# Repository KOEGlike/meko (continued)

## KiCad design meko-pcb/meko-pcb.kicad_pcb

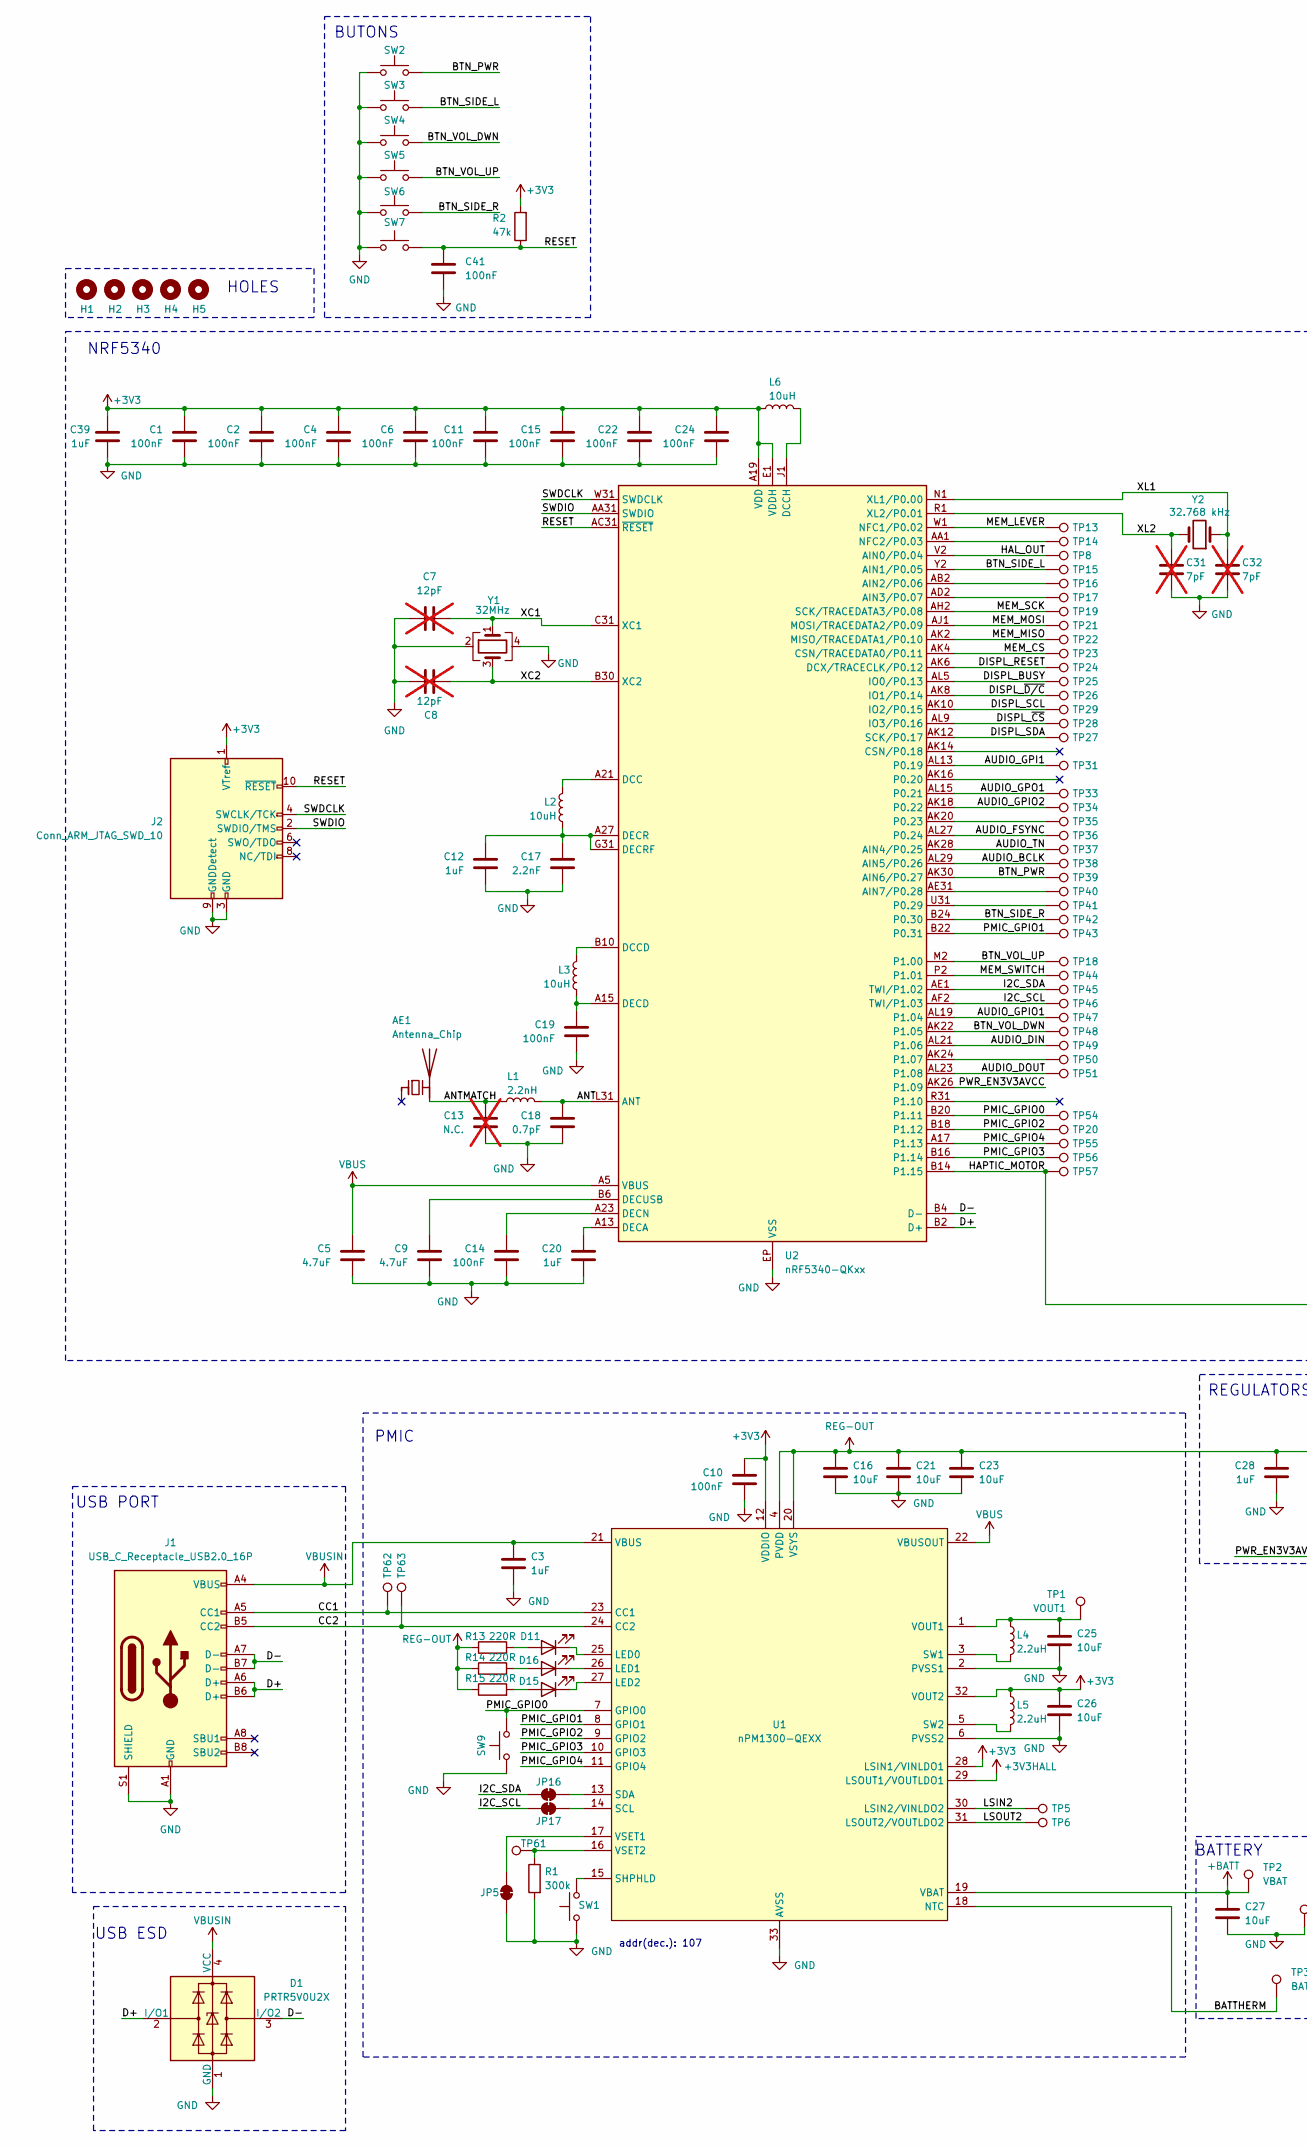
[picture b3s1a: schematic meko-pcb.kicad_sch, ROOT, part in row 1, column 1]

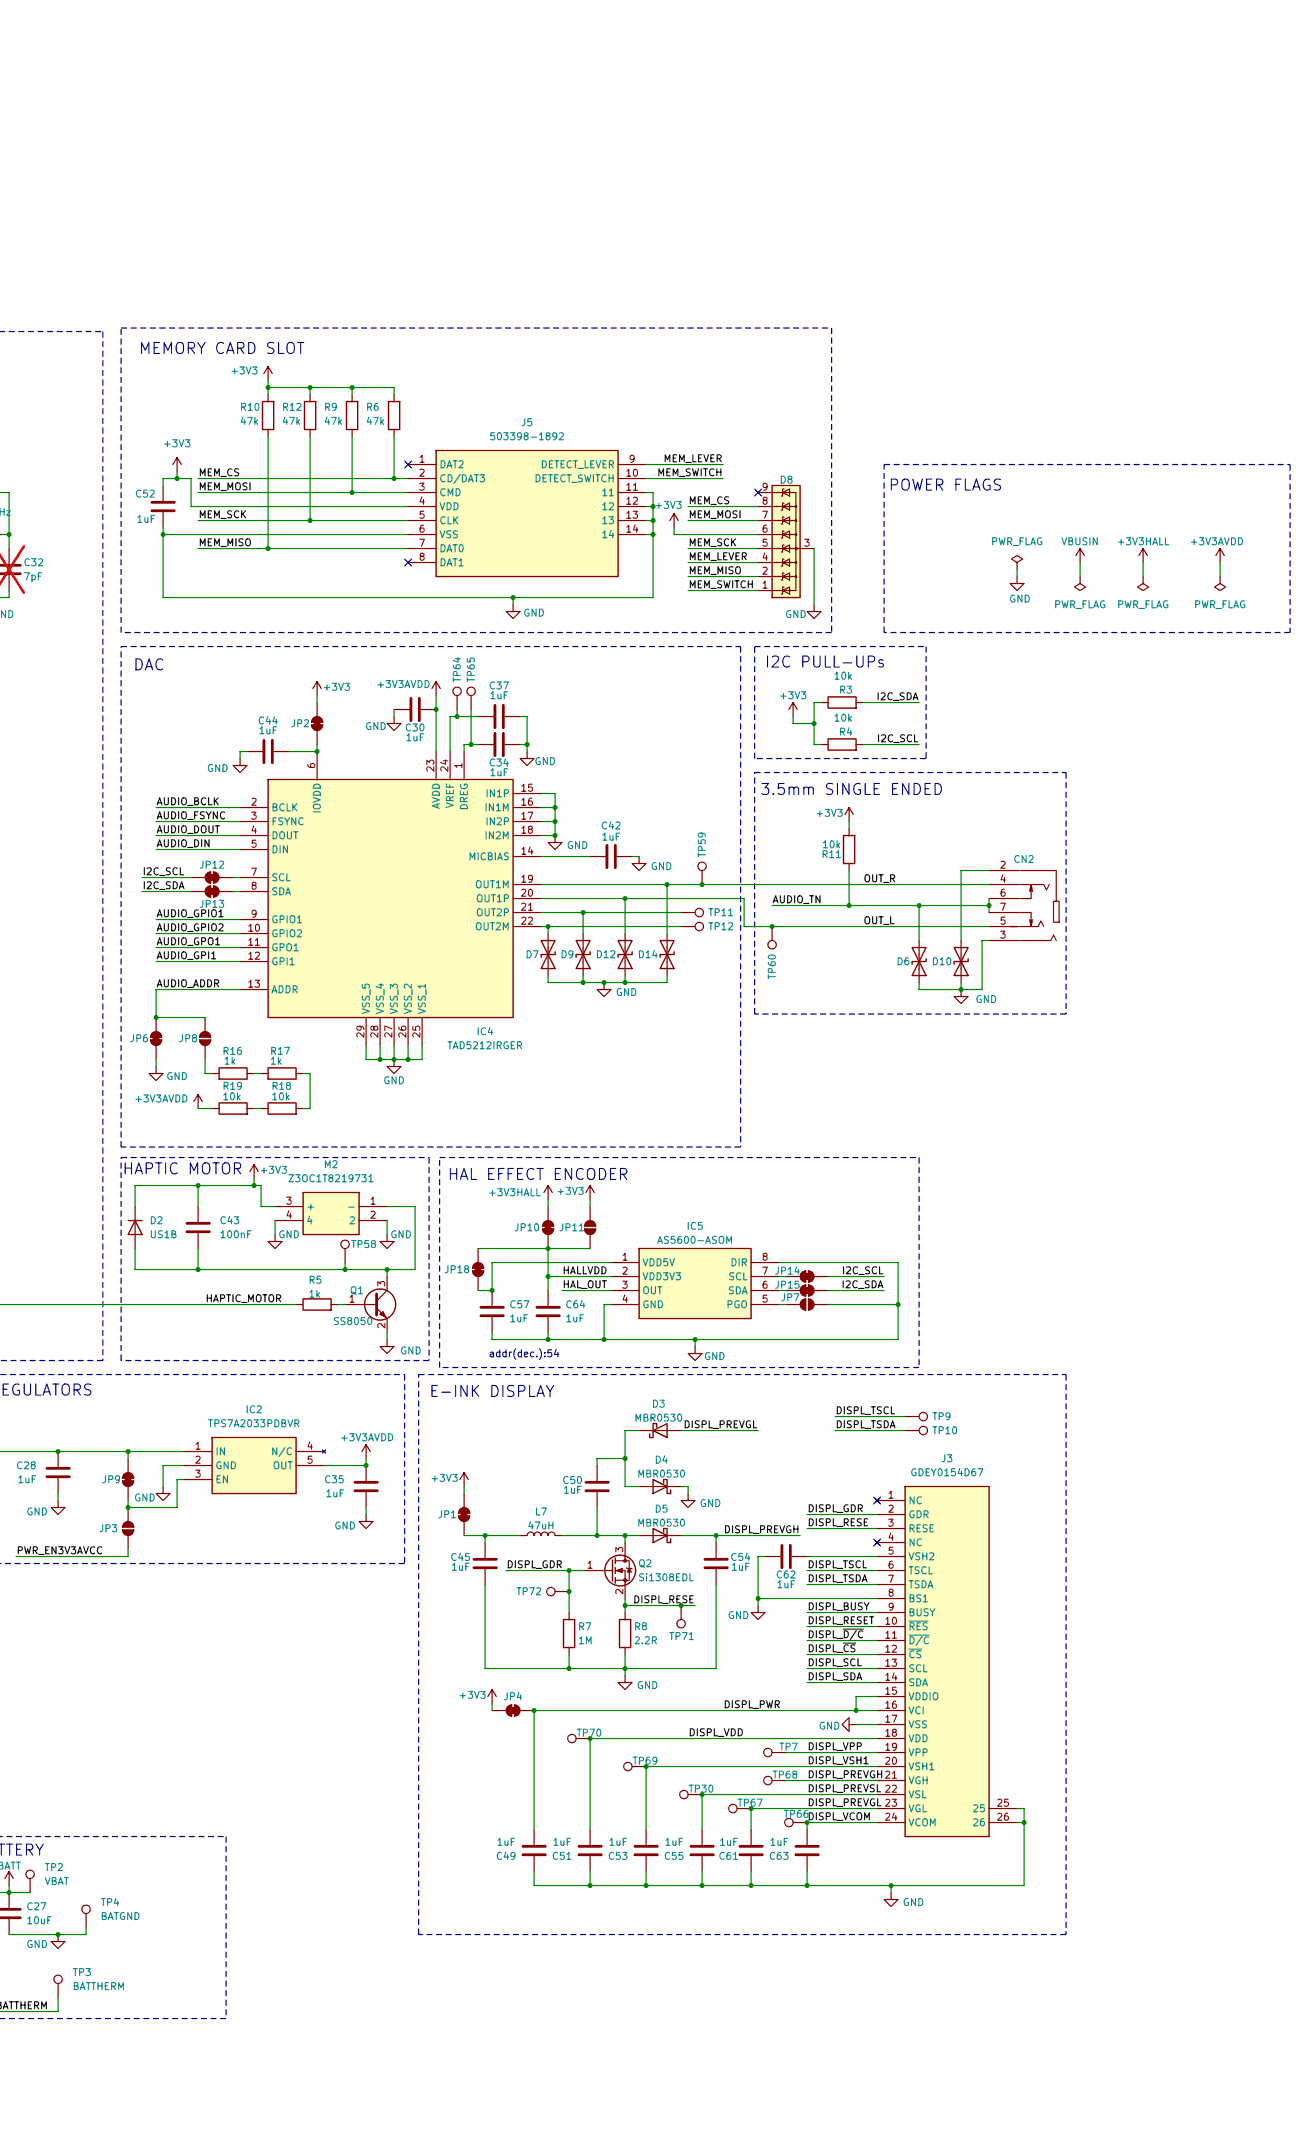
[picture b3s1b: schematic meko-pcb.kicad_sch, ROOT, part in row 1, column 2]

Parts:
AE1: Antenna_Chip; D_1206_3216Metric; MPN ANT3216LL00R2400A; LCSC C293767
C1, C2, C4, C6, C10, C11, C14, C15, C19, C22, C24, C41, C43: 100nF; C_0603_1608Metric; MPN CC0603KRX7R9BB104; LCSC C14663
C3, C12, C20, C28, C30, C34, C35, C37, C39, C42, C44, C45, C49, C50, C51, C52, C53, C54, C55, C57, C61, C62, C63, C64: 1uF; C_0603_1608Metric; MPN CL10A105KB8NNNC; LCSC C15849
C5, C9: 4.7uF; C_0603_1608Metric; MPN CL10A475KP8NNNC; LCSC C19666
C7, C8: 12pF; C_0603_1608Metric; MPN CL10C120JB8NNNC; LCSC C38523; not fitted
C13: N.C.; C_0603_1608Metric; not fitted
C16, C21, C23, C25, C26, C27: 10uF; C_0603_1608Metric; MPN CL10A106KP8NNNC; LCSC C19702
C17: 2.2nF; C_0603_1608Metric; MPN FCC0603B222K500CT; LCSC C5137562
C18: 0.7pF; C_0603_1608Metric; MPN CC0603BRNPO9BNR70; LCSC C501844
C31, C32: 7pF; C_0603_1608Metric; not fitted
CN2: AUDIO-SMD_PJ-342; MPN PJ-342; LCSC Part Name 3.5mm耳机座
D1: PRTR5V0U2X; SOT-143; MPN PRTR5V0U2X,215; LCSC C12333
D2: US1B; D_SMA; MPN US1B; LCSC C18199126
D3, D4, D5: MBR0530; D_SOD-123; MPN MBR0530T1G; LCSC C82046
D6, D7, D9, D10, D12, D14: D_TVS; D_SOD-323F; MPN PESD5V0V1BA; LCSC C29779756
D8: D3V3X8U9LP3810; Diodes_UDFN3810-9_TYPE_B-better-pinout; MPN D3V3F8U9LP3810-7; LCSC C3715130
D11: Orange; LED_0603_1608Metric; MPN XL-1608UOC-06; LCSC C965800
D15: white; LED_0603_1608Metric; MPN XL-1608UWC-04; LCSC C965808
D16: blue; LED_0603_1608Metric; MPN F.0603.00048/P2-0603W6YS2-06T-002; LCSC C7496823
H1, H2, H3, H4, H5: MountingHole; MountingHole_1.8mm_M1.6
IC2: TPS7A2033PDBVR; SOT95P280X145-5N; MPN TPS7A2033PDBVR; Mouser Part Number 595-TPS7A2033PDBVR
IC4: TAD5212IRGER; TAD5112IRGER; MPN TAD5212IRGER; LCSC C45068920
IC5: AS5600-ASOM; SOIC127P600X175-8N; MPN AS5600-ASOT; LCSC C499458
J1: USB_C_Receptacle_USB2.0_16P; USB_C_Receptacle_G-Switch_GT-USB-7010ASV; MPN GT-USB-7010ASV; LCSC C2988369
J2: Conn_ARM_JTAG_SWD_10; PinHeader_2x05_P1.27mm_Vertical
J3: GDEY0154D67; FPC-SMD_24P-P0.50_FPC-05FB-24PH20; MPN FPC-05FB-24PH20; Mouser Part Number 798-FH34SRJ24S05SH99
J5: 503398-1892; 5033981892; MPN 503398-1892; Mouser Part Number 538-503398-1892
JP1, JP2, JP4, JP5, JP6, JP9, JP10, JP12, JP13, JP14, JP15, JP16, JP17, JP18: SolderJumper_2_Bridged; SolderJumper-2_P1.3mm_Bridged_RoundedPad1.0x1.5mm
JP3, JP7, JP8, JP11: SolderJumper_2_Open; SolderJumper-2_P1.3mm_Open_RoundedPad1.0x1.5mm
L1: 2.2nH; L_0603_1608Metric; MPN LQG18HN2N2S00D; LCSC C113061
L2, L3, L6: 10uH; L_0805_2012Metric; MPN SLM2012100MIT; LCSC C2831365
L4, L5: 2.2uH; L_0805_2012Metric; MPN DFE201210U-2R2M=P2; LCSC C2049745
L7: 47uH; L_0805_2012Metric; MPN MLZ2012M470WT000; LCSC C383408
M2: Z3OC1T8219731; Manufacturer_Part_Number Z3OC1T8219731; LCSC C2894731
Q1: SS8050; SOT-23; MPN SS8050-HF; LCSC C5179688
Q2: Si1308EDL; SOT-323_SC-70; MPN SI1308EDL-T1-GE3; LCSC C469327
R1: 300k; R_0603_1608Metric; MPN FRC0603F3003TS; LCSC C23024
R2, R6, R9, R10, R12: 47k; R_0603_1608Metric; MPN FRC0603F4702TS; LCSC C25819
R3, R4, R11, R18, R19: 10k; R_0603_1608Metric; MPN 0603WAF1002T5E; LCSC C25804
R5, R16, R17: 1k; R_0603_1608Metric; MPN RC0603FR-071KL; LCSC C21190
R7: 1M; R_0603_1608Metric; MPN RC0603FR-071ML; LCSC C22935
R8: 2.2R; R_0603_1608Metric; MPN FRC0603J2R2TS; LCSC C2930032
R13, R14, R15: 220R; R_0603_1608Metric; MPN RC0603FR-07220RL; LCSC C22962
SW1, SW7, SW9: SW_Push; SW_Push_SPST_NO_Alps_SKRK; MPN TS-1088-AR02016; LCSC C720477
SW2, SW3, SW4, SW5, SW6: SW_Push; SW_Push_1P1T-MP_NO_Horizontal_Alps_SKRTLAE010; MPN SKRTLAE010; LCSC C110293
TP1: VOUT1; TestPoint_Pad_D1.0mm
TP2: VBAT; TestPoint_Pad_D1.5mm
TP3: BATTHERM; TestPoint_Pad_D1.5mm
TP4: BATGND; TestPoint_Pad_D1.5mm
TP5, TP11, TP13, TP15, TP18, TP19, TP20, TP23, TP26, TP29, TP35, TP38, TP41, TP46, TP49, TP63, TP65: DISPL_SCL; TestPoint_Pad_D1.0mm
TP6, TP7, TP8, TP9, TP10, TP12, TP14, TP16, TP17, TP21, TP22, TP24, TP25, TP27, TP28, TP30, TP31, TP33, TP34, TP36, TP37, TP39, TP40, TP42, TP43, TP44, TP45, TP47, TP48, TP50, TP51, TP54, TP55, TP56, TP57, TP58, TP59, TP60, TP61, TP62, TP64, TP66, TP67, TP68, TP69, TP70, TP71, TP72: DISPL_SDA; TestPoint_Pad_D1.0mm
U1: nPM1300-QEXX; QFN-32-1EP_5x5mm_P0.5mm_EP3.6x3.6mm_ThermalVias; MPN nPM1300-QEAA-R7; LCSC C7501206
U2: nRF5340-QKxx; Nordic_AQFN-94-1EP_7x7mm_P0.4mm; MPN NRF5340-QKAA-R; LCSC C3015611
Y1: 32MHz; Crystal_SMD_2520-4Pin_2.5x2.0mm; MPN 2TJ432000NYFBC; LCSC C2149238
Y2: 32.768 kHz; Crystal_SMD_3215-2Pin_3.2x1.5mm; MPN XKXGI-SUA-32.768K; LCSC C90945

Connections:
+3V3: C1.1, C2.1, C4.1, C6.1, C10.1, C11.1, C15.1, C22.1, C24.1, C26.1, C39.1, C43.1, C52.1, D2.1 (K), D8.6 (Line-7), J2.1 (VTref), J5.4 (VDD), JP1.2 (B), JP2.2 (B), JP4.2 (B), JP11.1 (A), L5.1, L6.2, M2.3 (+), R2.2, R3.1, R4.1, R6.2, R9.2, R10.2, R11.2, R12.2, U1.12 (VDDIO), U1.28 (LSIN1/VINLDO1), U1.32 (VOUT2), U2.A19 (VDD), U2.AC1 (VDD), U2.AG1 (VDD), U2.AJ31 (VDD), U2.AL3 (VDD), U2.AL7 (VDD), U2.AL11 (VDD), U2.AL17 (VDD), U2.AL25 (VDD), U2.B8 (VDD), U2.B28 (VDD), U2.C1 (VDD), U2.E1 (VDDH), U2.E31 (VDD), U2.L1 (VDD), U2.N31 (VDD), U2.U1 (VDD)
+3V3AVDD: C30.1, C35.1, IC2.5 (OUT), IC4.23 (AVDD), R19.1
+3V3HALL: JP10.2 (B), U1.29 (LSOUT1/VOUTLDO1)
+BATT: C27.1, TP2.1, U1.19 (VBAT)
/ANT: C18.1, L1.1, U2.L31 (ANT)
/ANTMATCH: AE1.2 (PCB_Trace), C13.1, L1.2
/AUDIO_ADDR: IC4.13 (ADDR), JP6.2 (B), JP8.1 (A)
/AUDIO_BCLK: IC4.2 (BCLK), TP38.1, U2.AL29 (AIN5/P0.26)
/AUDIO_DIN: IC4.5 (DIN), TP49.1, U2.AL21 (P1.06)
/AUDIO_DOUT: IC4.4 (DOUT), TP51.1, U2.AL23 (P1.08)
/AUDIO_FSYNC: IC4.3 (FSYNC), TP36.1, U2.AL27 (P0.24)
/AUDIO_GPI1: IC4.12 (GPI1), TP31.1, U2.AL13 (P0.19)
/AUDIO_GPIO1: IC4.9 (GPIO1), TP47.1, U2.AL19 (P1.04)
/AUDIO_GPIO2: IC4.10 (GPIO2), TP34.1, U2.AK18 (P0.22)
/AUDIO_GPO1: IC4.11 (GPO1), TP33.1, U2.AL15 (P0.21)
/AUDIO_TN: CN2.6, CN2.7, D6.2 (A2), R11.1, TP37.1, U2.AK28 (AIN4/P0.25)
/BATTHERM: TP3.1, U1.18 (NTC)
/BTN_PWR: SW2.2, TP39.1, U2.AK30 (AIN6/P0.27)
/BTN_SIDE_L: SW3.2, TP15.1, U2.Y2 (AIN1/P0.05)
/BTN_SIDE_R: SW6.2, TP42.1, U2.B24 (P0.30)
/BTN_VOL_DWN: SW4.2, TP48.1, U2.AK22 (P1.05)
/BTN_VOL_UP: SW5.2, TP18.1, U2.M2 (P1.00)
/CC1: J1.A5 (CC1), TP62.1, U1.23 (CC1)
/CC2: J1.B5 (CC2), TP63.1, U1.24 (CC2)
/D+: D1.2 (I/O1), J1.A6 (D+), J1.B6 (D+), U2.B2 (D+)
/D-: D1.3 (I/O2), J1.A7 (D-), J1.B7 (D-), U2.B4 (D-)
/DISPL_BUSY: J3.9 (BUSY), TP25.1, U2.AL5 (IO0/P0.13)
/DISPL_GDR: J3.2 (GDR), Q2.1 (G), R7.1, TP72.1
/DISPL_PREVGH: C54.2, D5.1 (K), J3.21 (VGH), TP68.1
/DISPL_PREVGL: C61.2, D3.2 (A), J3.23 (VGL), TP67.1
/DISPL_PREVSL: C55.2, J3.22 (VSL), TP30.1
/DISPL_PWR: C49.2, J3.15 (VDDIO), J3.16 (VCI), JP4.1 (A)
/DISPL_RESE: J3.3 (RESE), Q2.2 (S), R8.1, TP71.1
/DISPL_RESET: J3.10 (~RES), TP24.1, U2.AK6 (DCX/TRACECLK/P0.12)
/DISPL_SCL: J3.13 (SCL), TP29.1, U2.AK10 (IO2/P0.15)
/DISPL_SDA: J3.14 (SDA), TP27.1, U2.AK12 (SCK/P0.17)
/DISPL_TSCL: J3.6 (TSCL), TP9.1
/DISPL_TSDA: J3.7 (TSDA), TP10.1
/DISPL_VCOM: C63.2, J3.24 (VCOM), TP66.1
/DISPL_VDD: C51.2, J3.18 (VDD), TP70.1
/DISPL_VPP: J3.19 (VPP), TP7.1
/DISPL_VSH1: C53.2, J3.20 (VSH1), TP69.1
/DISPL_~CS: J3.12 (~CS), TP28.1, U2.AL9 (IO3/P0.16)
/DISPL_~D/C: J3.11 (~D/C), TP26.1, U2.AK8 (IO1/P0.14)
/HALLVDD: C64.1, IC5.2 (VDD3V3), JP10.1 (A), JP11.2 (B), JP18.2 (B)
/HAL_OUT: IC5.3 (OUT), TP8.1, U2.V2 (AIN0/P0.04)
/HAPTIC_MOTOR: R5.1, TP57.1, U2.B14 (P1.15)
/I2C_SCL: JP12.1 (A), JP14.2 (B), JP17.1 (A), R4.2, TP46.1, U2.AF2 (TWI/P1.03)
/I2C_SDA: JP13.1 (A), JP15.2 (B), JP16.1 (A), R3.2, TP45.1, U2.AE1 (TWI/P1.02)
/LSIN2: TP5.1, U1.30 (LSIN2/VINLDO2)
/LSOUT2: TP6.1, U1.31 (LSOUT2/VOUTLDO2)
/MEM_CS: D8.8 (Line-4), J5.2 (CD/DAT3), R6.1, TP23.1, U2.AK4 (CSN/TRACEDATA0/P0.11)
/MEM_LEVER: D8.4 (Line-6), J5.9 (DETECT_LEVER), TP13.1, U2.W1 (NFC1/P0.02)
/MEM_MISO: D8.2 (Line-3), J5.7 (DAT0), R10.1, TP22.1, U2.AK2 (MISO/TRACEDATA1/P0.10)
/MEM_MOSI: D8.7 (Line-5), J5.3 (CMD), R9.1, TP21.1, U2.AJ1 (MOSI/TRACEDATA2/P0.09)
/MEM_SCK: D8.5 (Line-8), J5.5 (CLK), R12.1, TP19.1, U2.AH2 (SCK/TRACEDATA3/P0.08)
/MEM_SWITCH: D8.1 (Line-1), J5.10 (DETECT_SWITCH), TP44.1, U2.P2 (P1.01)
/OUT_L: CN2.5, D12.2 (A2), IC4.20 (OUT1P), TP60.1
/OUT_R: CN2.4, D14.2 (A2), IC4.19 (OUT1M), TP59.1
/PMIC_GPIO0: SW9.2, TP54.1, U1.7 (GPIO0), U2.B20 (P1.11)
/PMIC_GPIO1: TP43.1, U1.8 (GPIO1), U2.B22 (P0.31)
/PMIC_GPIO2: TP20.1, U1.9 (GPIO2), U2.B18 (P1.12)
/PMIC_GPIO3: TP56.1, U1.10 (GPIO3), U2.B16 (P1.14)
/PMIC_GPIO4: TP55.1, U1.11 (GPIO4), U2.A17 (P1.13)
/PWR_EN3V3AVCC: JP3.2 (B), U2.AK26 (P1.09)
/RESET: C41.1, J2.10 (~RESET), R2.1, SW7.2, U2.AC31 (~RESET)
/SWDCLK: J2.4 (SWCLK/TCK), U2.W31 (SWDCLK)
/SWDIO: J2.2 (SWDIO/TMS), U2.AA31 (SWDIO)
/XC1: C7.1, U2.C31 (XC1), Y1.1
/XC2: C8.1, U2.B30 (XC2), Y1.3
/XL1: C32.1, U2.N1 (XL1/P0.00), Y2.1
/XL2: C31.1, U2.R1 (XL2/P0.01), Y2.2
GND: C1.2, C2.2, C3.2, C4.2, C5.2, C6.2, C7.2, C8.2, C9.2, C10.2, C11.2, C12.2, C13.2, C14.2, C15.2, C16.2, C17.2, C18.2, C19.2, C20.2, C21.2, C22.2, C23.2, C24.2, C25.2, C26.2, C27.2, C28.2, C30.2, C31.2, C32.2, C34.1, C35.2, C37.2, C39.2, C41.2, C42.2, C44.1, C45.1, C49.1, C51.1, C52.2, C53.1, C54.1, C55.1, C57.2, C61.1, C62.1, C63.1, C64.2, CN2.3, D1.1 (GND), D4.1 (K), D6.1 (A1), D7.1 (A1), D8.3 (GND), D9.1 (A1), D10.1 (A1), D12.1 (A1), D14.1 (A1), IC2.2 (GND), IC4.15 (IN1P), IC4.16 (IN1M), IC4.17 (IN2P), IC4.18 (IN2M), IC4.25 (VSS_1), IC4.26 (VSS_2), IC4.27 (VSS_3), IC4.28 (VSS_4), IC4.29 (VSS_5), IC5.4 (GND), IC5.8 (DIR), J1.A1 (GND), J1.A12 (GND), J1.B1 (GND), J1.B12 (GND), J1.S1 (SHIELD), J2.3 (GND), J2.5 (GND), J2.9 (GNDDetect), J3.8 (BS1), J3.17 (VSS), J3.25, J3.26, J5.6 (VSS), J5.11, J5.12, J5.13, J5.14, JP5.1 (A), JP6.1 (A), JP7.1 (A), M2.2, M2.4, Q1.2 (E), R1.2, R7.2, R8.2, SW1.1, SW2.1, SW3.1, SW4.1, SW5.1, SW6.1, SW7.1, SW9.1, TP4.1, U1.2 (PVSS1), U1.6 (PVSS2), U1.33 (AVSS), U2.EP (VSS), Y1.2, Y1.4
unnamed: C43.2, D2.2 (A), M2.1 (-), Q1.3 (C), TP58.1
unnamed: C50.2, D3.1 (K), D4.2 (A)
unnamed: C50.1, D5.2 (A), L7.2, Q2.3 (D)
unnamed: D7.2 (A2), IC4.22 (OUT2M), TP12.1
unnamed: D9.2 (A2), IC4.21 (OUT2P), TP11.1
unnamed: CN2.2, D10.2 (A2)
unnamed: D11.2 (A), R13.2
unnamed: D11.1 (K), U1.25 (LED0)
unnamed: D15.2 (A), R15.2
unnamed: D15.1 (K), U1.27 (LED2)
unnamed: D16.2 (A), R14.2
unnamed: D16.1 (K), U1.26 (LED1)
unnamed: IC2.3 (EN), JP3.1 (A), JP9.1 (A)
unnamed: C34.2, IC4.1 (DREG), TP65.1
unnamed: C44.2, IC4.6 (IOVDD), JP2.1 (A)
unnamed: C42.1, IC4.14 (MICBIAS)
unnamed: IC4.7 (SCL), JP12.2 (B)
unnamed: IC4.8 (SDA), JP13.2 (B)
unnamed: C37.1, IC4.24 (VREF), TP64.1
unnamed: IC5.5 (PGO), JP7.2 (B)
unnamed: IC5.7 (SCL), JP14.1 (A)
unnamed: IC5.6 (SDA), JP15.1 (A)
unnamed: C57.1, IC5.1 (VDD5V), JP18.1 (A)
unnamed: C62.2, J3.5 (VSH2)
unnamed: C45.2, JP1.1 (A), L7.1
unnamed: JP5.2 (B), U1.17 (VSET1)
unnamed: JP8.2 (B), R16.2
unnamed: JP16.2 (B), U1.13 (SDA)
unnamed: JP17.2 (B), U1.14 (SCL)
unnamed: Q1.1 (B), R5.2
unnamed: R16.1, R17.2
unnamed: R17.1, R18.2
unnamed: R18.1, R19.2
unnamed: SW1.2, U1.15 (SHPHLD)
unnamed: L4.2, U1.3 (SW1)
unnamed: L5.2, U1.5 (SW2)
unnamed: C25.1, L4.1, TP1.1, U1.1 (VOUT1)
unnamed: R1.1, TP61.1, U1.16 (VSET2)
unnamed: TP16.1, U2.AB2 (AIN2/P0.06)
unnamed: TP17.1, U2.AD2 (AIN3/P0.07)
unnamed: TP40.1, U2.AE31 (AIN7/P0.28)
unnamed: L2.1, U2.A21 (DCC)
unnamed: L3.1, U2.B10 (DCCD)
unnamed: L6.1, U2.J1 (DCCH)
unnamed: C20.1, U2.A13 (DECA)
unnamed: C19.1, L3.2, U2.A15 (DECD)
unnamed: C14.1, U2.A23 (DECN)
unnamed: C12.1, C17.1, L2.2, U2.A27 (DECR), U2.G31 (DECRF)
unnamed: C9.1, U2.B6 (DECUSB)
unnamed: TP14.1, U2.AA1 (NFC2/P0.03)
unnamed: TP35.1, U2.AK20 (P0.23)
unnamed: TP41.1, U2.U31 (P0.29)
unnamed: TP50.1, U2.AK24 (P1.07)
REG-OUT: C16.1, C21.1, C23.1, C28.1, IC2.1 (IN), JP9.2 (B), R13.1, R14.1, R15.1, U1.4 (PVDD), U1.20 (VSYS)
VBUS: C5.1, U1.22 (VBUSOUT), U2.A5 (VBUS)
VBUSIN: C3.1, D1.4 (VCC), J1.A4 (VBUS), J1.A9 (VBUS), J1.B4 (VBUS), J1.B9 (VBUS), U1.21 (VBUS)

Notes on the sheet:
USB ESD
REGULATORS
USB PORT
POWER FLAGS
HOLES
addr(dec.):54
E-INK DISPLAY
I2C PULL-UPs
MEMORY CARD SLOT
BUTONS
NRF5340
HAPTIC MOTOR
PMIC
addr(dec.): 107
BATTERY
DAC
HAL EFFECT ENCODER
3.5mm SINGLE ENDED

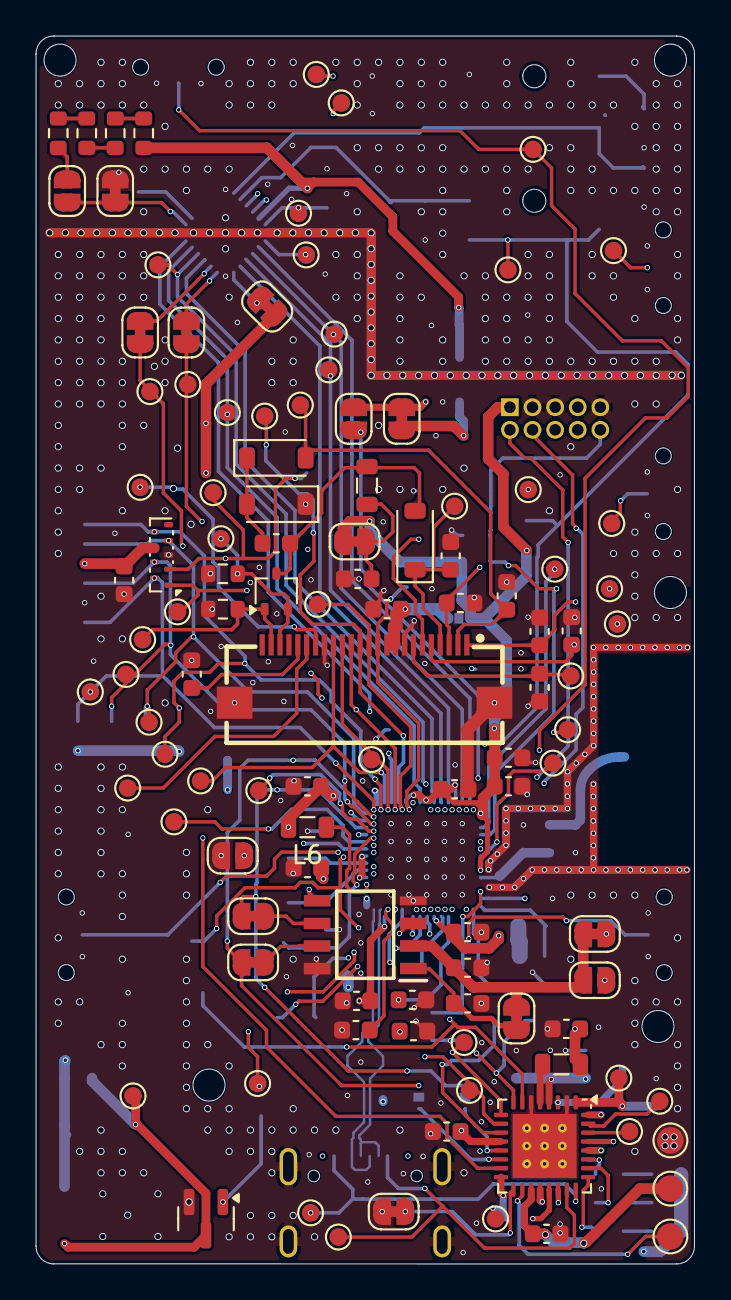
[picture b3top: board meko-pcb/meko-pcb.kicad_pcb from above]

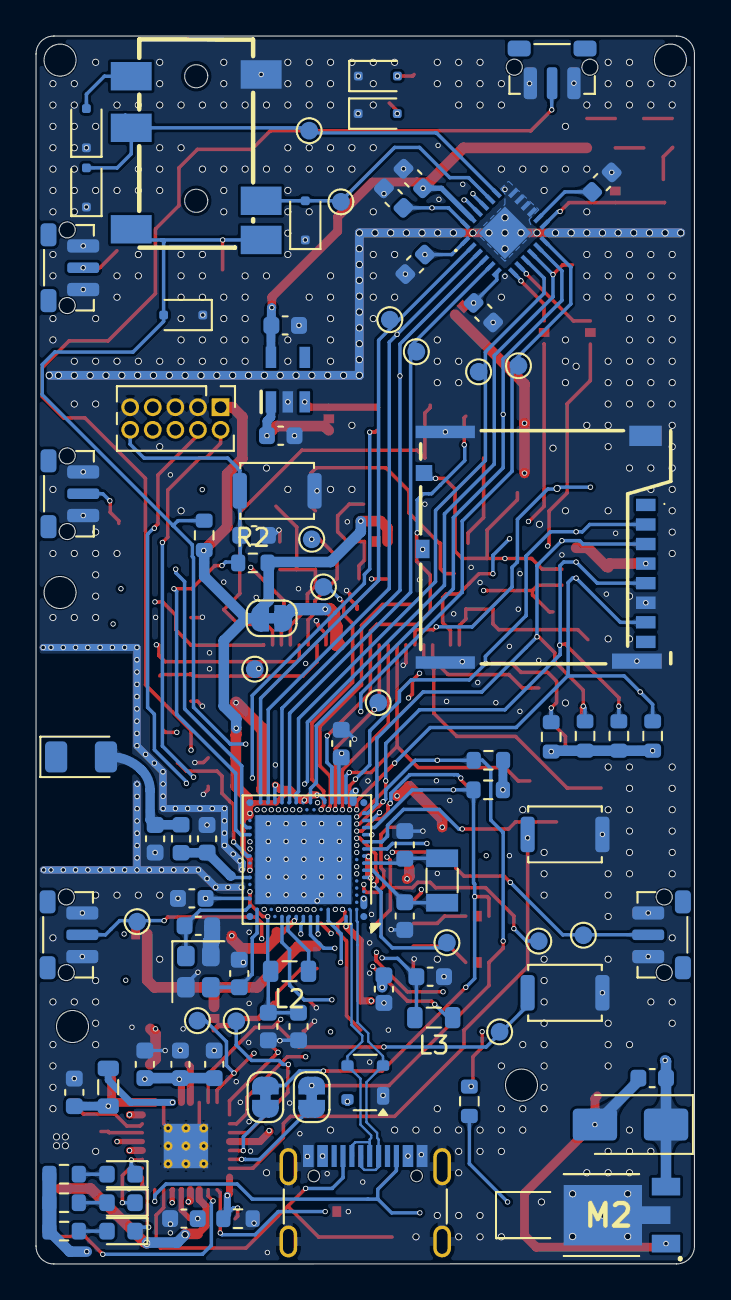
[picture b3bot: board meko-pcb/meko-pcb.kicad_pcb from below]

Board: 6 copper layers, 37.0 x 69.0 mm, 209 parts (94 on the bottom side), 129 nets.

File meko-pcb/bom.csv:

"Designator","Quantity","Value","LCSC Part #","Footprint"
"AE1","1","Antenna_Chip","C293767","Diode_SMD:D_1206_3216Metric"
"C1,C2,C4,C6,C10,C11,C14,C15,C19,C22,C24,C41,C43","13","100nF","C14663","Capacitor_SMD:C_0603_1608Metric"
"C3,C12,C20,C28,C30,C34,C35,C37,C39,C42,C44,C45,C49,C50,C51,C52,C53,C54,C55,C57,C61,C62,C63,C64","24","1uF","C15849","Capacitor_SMD:C_0603_1608Metric"
"C5,C9","2","4.7uF","C19666","Capacitor_SMD:C_0603_1608Metric"
"C7,C8","2","12pF","C38523","Capacitor_SMD:C_0603_1608Metric"
"C16,C21,C23,C25,C26,C27","6","10uF","C19702","Capacitor_SMD:C_0603_1608Metric"
"C17","1","2.2nF","C5137562","Capacitor_SMD:C_0603_1608Metric"
"C18","1","0.7pF","C501844","Capacitor_SMD:C_0603_1608Metric"
"D1","1","PRTR5V0U2X","C12333","Package_TO_SOT_SMD:SOT-143"
"D2","1","US1B","C18199126","Diode_SMD:D_SMA"
"D3,D4,D5","3","MBR0530","C82046","Diode_SMD:D_SOD-123"
"D6,D7,D9,D10,D12,D14","6","D_TVS","C29779756","Diode_SMD:D_SOD-323F"
"D8","1","D3V3X8U9LP3810","C3715130","Diodes_UDFN3810-9_TYPE_B-better-pinout:Diodes_UDFN3810-9_TYPE_B-better-pinout"
"D11","1","Orange","C965800","LED_SMD:LED_0603_1608Metric"
"D15","1","white","C965808","LED_SMD:LED_0603_1608Metric"
"D16","1","blue","C7496823","LED_SMD:LED_0603_1608Metric"
"IC2","1","TPS7A2033PDBVR","C2862740","TPS7A2018PDBVR:SOT95P280X145-5N"
"IC4","1","TAD5212IRGER","C45068920","TAD5112IRGER:TAD5112IRGER"
"IC5","1","AS5600-ASOM","C499458","AS5600-ASOM:SOIC127P600X175-8N"
"J1","1","USB_C_Receptacle_USB2.0_16P","C2988369","Connector_USB:USB_C_Receptacle_G-Switch_GT-USB-7010ASV"
"J3","1","GDEY0154D67","C2856831","FPC-SMD_24P-P0.50_FPC-05FB-24PH20:FPC-SMD_24P-P0.50_FPC-05FB-24PH20"
"J5","1","503398-1892","C428492","503398-1892:5033981892"
"L1","1","2.2nH","C113061","Inductor_SMD:L_0603_1608Metric"
"L2,L3,L6","3","10uH","C2831365","Inductor_SMD:L_0805_2012Metric"
"L4,L5","2","2.2uH","C2049745","Inductor_SMD:L_0805_2012Metric"
"L7","1","47uH","C383408","Inductor_SMD:L_0805_2012Metric"
"M1","1","~","C2894731","LD-SM-430:SMD_LD-SM-430-1"
"Q1","1","SS8050","C5179688","Package_TO_SOT_SMD:SOT-23"
"Q2","1","Si1308EDL","C469327","Package_TO_SOT_SMD:SOT-323_SC-70"
"R1","1","300k","C23024","Resistor_SMD:R_0603_1608Metric"
"R2,R6,R9,R10,R12","5","47k","C25819","Resistor_SMD:R_0603_1608Metric"
"R3,R4,R11,R18,R19","5","10k","C25804","Resistor_SMD:R_0603_1608Metric"
"R5,R16,R17","3","1k","C21190","Resistor_SMD:R_0603_1608Metric"
"R7","1","1M","C22935","Resistor_SMD:R_0603_1608Metric"
"R8","1","2.2R","C2930032","Resistor_SMD:R_0603_1608Metric"
"R13,R14,R15","3","220R","C22962","Resistor_SMD:R_0603_1608Metric"
"SW1,SW7,SW9","3","SW_Push","C720477","Button_Switch_SMD:SW_Push_SPST_NO_Alps_SKRK"
"SW2,SW3,SW4,SW5,SW6","5","SW_Push","C110293","Button_Switch_SMD:SW_Push_1P1T-MP_NO_Horizontal_Alps_SKRTLAE010"
"U1","1","nPM1300-QEXX","C7501206","Package_DFN_QFN:QFN-32-1EP_5x5mm_P0.5mm_EP3.6x3.6mm_ThermalVias"
"U2","1","nRF5340-QKxx","C3015611","Package_DFN_QFN:Nordic_AQFN-94-1EP_7x7mm_P0.4mm"
"Y1","1","32MHz","C2149238","Crystal:Crystal_SMD_2520-4Pin_2.5x2.0mm"
"Y2","1","32.768 kHz","C5213671","Crystal:Crystal_SMD_3215-2Pin_3.2x1.5mm"
"CN2","1","~","C668606","PJ-242:AUDIO-SMD_PJ-342"

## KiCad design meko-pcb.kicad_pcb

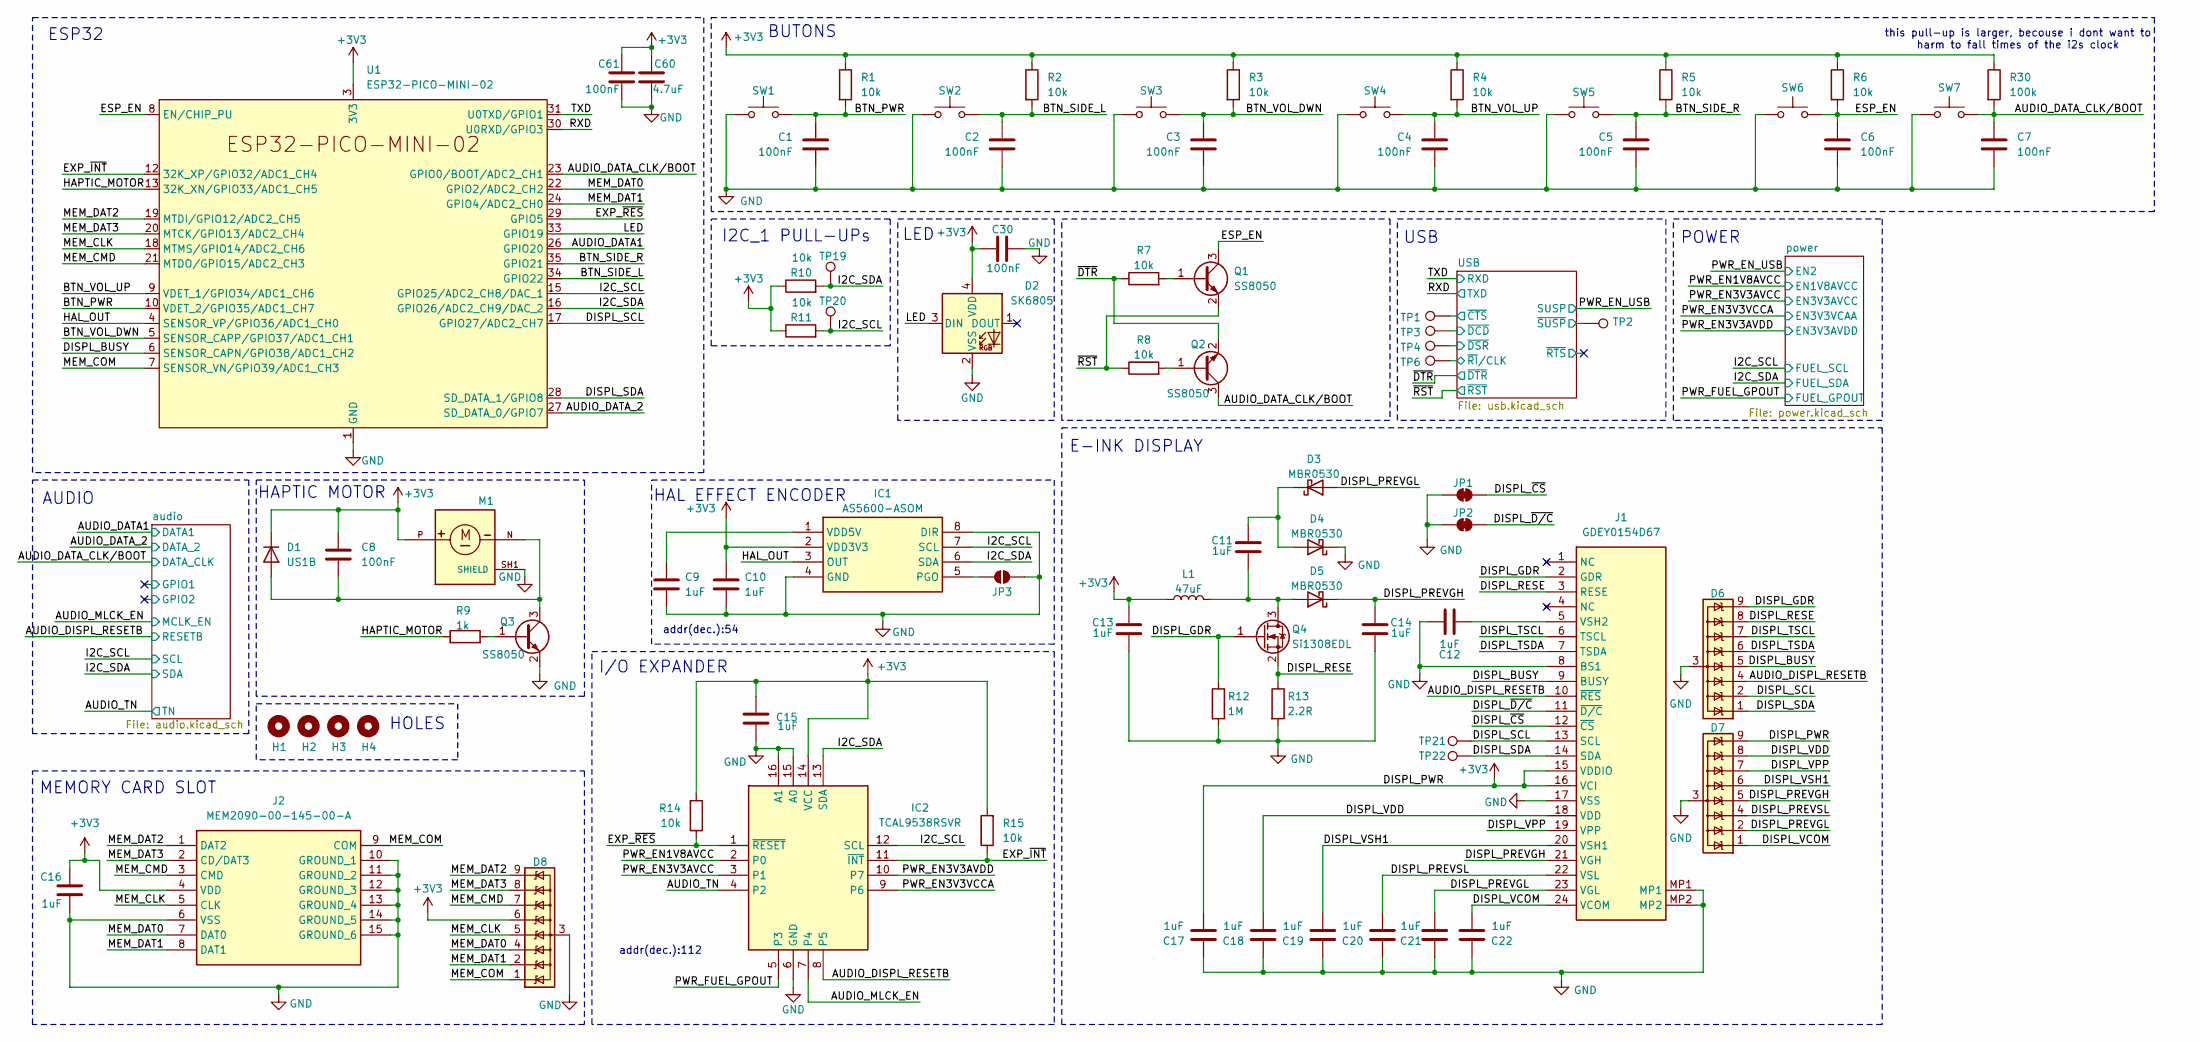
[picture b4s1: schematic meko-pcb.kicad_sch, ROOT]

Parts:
C1, C2, C3, C4, C5, C6, C7, C8, C30, C61: 100nF; C_0402_1005Metric
C9, C10, C11, C12, C13, C14, C15, C16, C17, C18, C19, C20, C21, C22: 1uF; C_0402_1005Metric
C60: 4.7uF; C_0402_1005Metric; LCSC C307423
D1: US1B; D_SMA
D2: SK6805; sk6805ec14
D3, D4, D5: MBR0530; D_SOD-123
D6, D7, D8: D3V3X8U9LP3810; Diodes_UDFN3810-9_TYPE_B-better-pinout
H1, H2, H3, H4: MountingHole; MountingHole_2.2mm_M2
IC1: AS5600-ASOM; SOIC127P600X175-8N; Manufacturer_Part_Number AS5600-ASOM; Mouser Part Number 985-AS5600-ASOM
IC2: TCAL9538RSVR; QFN40P180X260X55-16N; Manufacturer_Part_Number TCAL9538RSVR; Mouser Part Number 595-TCAL9538RSVR
J1: GDEY0154D67; FH34SRJ24S05SH99-disp; Manufacturer_Part_Number FH34SRJ-24S-0.5SH(99); Mouser Part Number 798-FH34SRJ24S05SH99
J2: MEM2090-00-145-00-A; MEM20900014500A; Manufacturer_Part_Number MEM2090-00-145-00-A; Mouser Part Number 640-MEM20900014500A
JP1, JP2: SolderJumper_2_Bridged; SolderJumper-2_P1.3mm_Bridged_RoundedPad1.0x1.5mm
JP3: SolderJumper_2_Open; SolderJumper-2_P1.3mm_Open_RoundedPad1.0x1.5mm
L1: 47uF; L_TDK_MLZ2012_h1.25mm
M1: HD-EMB1204-SM; PUI_HD-EMB1204-SM; PARTREV A; DigiKey_Part_Number 668-HD-EMB1204-SMTR-ND
Q1, Q2, Q3: SS8050; SOT-23
Q4: Si1308EDL; SOT-323_SC-70
R1, R2, R3, R4, R5, R6, R7, R8, R10, R11, R14, R15: 10k; R_0402_1005Metric
R9: 1k; R_0402_1005Metric
R12: 1M; R_0402_1005Metric
R13: 2.2R; R_0402_1005Metric
R30: 100k; R_0402_1005Metric
SW1, SW2, SW3, SW4, SW5: SW_Push; SW_Push_1P1T-MP_NO_Horizontal_Alps_SKRTLAE010
SW6, SW7: SW_Push; SW_Push_SPST_NO_Alps_SKRK
TP1, TP2, TP3, TP4, TP6, TP19, TP20, TP21, TP22: TestPoint; TestPoint_Pad_D1.0mm
U1: ESP32-PICO-MINI-02

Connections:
+3V3: C8.1, C10.1, C13.2, C15.2, C16.1, C17.2, C30.1, C60.2, C61.1, D1.1 (K), D2.4 (VDD), D7.9 (Line-2), D8.6 (Line-7), IC1.2 (VDD3V3), IC2.14 (VCC), J1.15 (VDDIO), J1.16 (VCI), J2.4 (VDD), L1.1, M1.P, R1.1, R2.1, R3.1, R4.1, R5.1, R6.1, R10.1, R11.1, R14.2, R15.2, R30.1, U1.3 (3V3); also elsewhere on the board
/AUDIO_DATA1: U1.26 (GPIO20); also elsewhere on the board
/AUDIO_DATA_2: U1.27 (SD_DATA_0/GPIO7); also elsewhere on the board
/AUDIO_DATA_CLK/BOOT: C7.1, Q2.3 (C), R30.2, SW7.2, U1.23 (GPIO0/BOOT/ADC2_CH1); also elsewhere on the board
/AUDIO_DISPL_RESETB: D6.4 (Line-6), IC2.8 (P5), J1.10 (~RES); also elsewhere on the board
/AUDIO_MLCK_EN: IC2.7 (P4); also elsewhere on the board
/AUDIO_TN: IC2.4 (P2); also elsewhere on the board
/BTN_PWR: C1.1, R1.2, SW1.2, U1.10 (VDET_2/GPIO35/ADC1_CH7)
/BTN_SIDE_L: C2.1, R2.2, SW2.2, U1.34 (GPIO22)
/BTN_SIDE_R: C5.1, R5.2, SW5.2, U1.35 (GPIO21)
/BTN_VOL_DWN: C3.1, R3.2, SW3.2, U1.5 (SENSOR_CAPP/GPIO37/ADC1_CH1)
/BTN_VOL_UP: C4.1, R4.2, SW4.2, U1.9 (VDET_1/GPIO34/ADC1_CH6)
/DISPL_BUSY: D6.5 (Line-8), J1.9 (BUSY), U1.6 (SENSOR_CAPN/GPIO38/ADC1_CH2)
/DISPL_GDR: D6.9 (Line-2), J1.2 (GDR), Q4.1 (G), R12.1
/DISPL_PREVGH: C14.2, D5.1 (K), D7.5 (Line-8), J1.21 (VGH)
/DISPL_PREVGL: C21.2, D3.2 (A), D7.2 (Line-3), J1.23 (VGL)
/DISPL_PREVSL: C20.2, D7.4 (Line-6), J1.22 (VSL)
/DISPL_RESE: D6.8 (Line-4), J1.3 (RESE), Q4.2 (S), R13.1
/DISPL_SCL: D6.2 (Line-3), J1.13 (SCL), TP21.1, U1.17 (GPIO27/ADC2_CH7)
/DISPL_SDA: D6.1 (Line-1), J1.14 (SDA), TP22.1, U1.28 (SD_DATA_1/GPIO8)
/DISPL_TSCL: D6.7 (Line-5), J1.6 (TSCL)
/DISPL_TSDA: D6.6 (Line-7), J1.7 (TSDA)
/DISPL_VCOM: C22.2, D7.1 (Line-1), J1.24 (VCOM)
/DISPL_VDD: C18.2, D7.8 (Line-4), J1.18 (VDD)
/DISPL_VPP: D7.7 (Line-5), J1.19 (VPP)
/DISPL_VSH1: C19.2, D7.6 (Line-7), J1.20 (VSH1)
/DISPL_~CS: J1.12 (~CS), JP1.2 (B)
/DISPL_~D/C: J1.11 (~D/C), JP2.2 (B)
/ESP_EN: C6.1, Q1.3 (C), R6.2, SW6.2, U1.8 (EN/CHIP_PU)
/EXP_~INT: IC2.11 (~INT), R15.1, U1.12 (32K_XP/GPIO32/ADC1_CH4)
/EXP_~RES: IC2.1 (~RESET), R14.1, U1.29 (GPIO5)
/HAL_OUT: IC1.3 (OUT), U1.4 (SENSOR_VP/GPIO36/ADC1_CH0)
/HAPTIC_MOTOR: R9.1, U1.13 (32K_XN/GPIO33/ADC1_CH5)
/I2C_SCL: IC1.7 (SCL), IC2.12 (SCL), R11.2, TP20.1, U1.15 (GPIO25/ADC2_CH8/DAC_1); also elsewhere on the board
/I2C_SDA: IC1.6 (SDA), IC2.13 (SDA), R10.2, TP19.1, U1.16 (GPIO26/ADC2_CH9/DAC_2); also elsewhere on the board
/LED: D2.3 (DIN), U1.33 (GPIO19)
/MEM_CLK: D8.5 (Line-8), J2.5 (CLK), U1.18 (MTMS/GPIO14/ADC2_CH6)
/MEM_CMD: D8.7 (Line-5), J2.3 (CMD), U1.21 (MTDO/GPIO15/ADC2_CH3)
/MEM_COM: D8.1 (Line-1), J2.9 (COM), U1.7 (SENSOR_VN/GPIO39/ADC1_CH3)
/MEM_DAT0: D8.4 (Line-6), J2.7 (DAT0), U1.22 (GPIO2/ADC2_CH2)
/MEM_DAT1: D8.2 (Line-3), J2.8 (DAT1), U1.24 (GPIO4/ADC2_CH0)
/MEM_DAT2: D8.9 (Line-2), J2.1 (DAT2), U1.19 (MTDI/GPIO12/ADC2_CH5)
/MEM_DAT3: D8.8 (Line-4), J2.2 (CD/DAT3), U1.20 (MTCK/GPIO13/ADC2_CH4)
/PWR_EN1V8AVCC: IC2.2 (P0); also elsewhere on the board
/PWR_EN3V3AVCC: IC2.3 (P1); also elsewhere on the board
/PWR_EN3V3AVDD: IC2.10 (P7); also elsewhere on the board
/PWR_EN3V3VCCA: IC2.9 (P6); also elsewhere on the board
/PWR_FUEL_GPOUT: IC2.5 (P3); also elsewhere on the board
/RXD: U1.30 (U0RXD/GPIO3); also elsewhere on the board
/TXD: U1.31 (U0TXD/GPIO1); also elsewhere on the board
/USB/~CTS: TP1.1; also elsewhere on the board
/USB/~DCD: TP3.1; also elsewhere on the board
/USB/~DSR: TP4.1; also elsewhere on the board
/USB/~RI/CLK: TP6.1; also elsewhere on the board
/USB/~SUSP: TP2.1; also elsewhere on the board
/~DTR: Q2.2 (E), R7.1; also elsewhere on the board
/~RST: Q1.2 (E), R8.1; also elsewhere on the board
GND: C1.2, C2.2, C3.2, C4.2, C5.2, C6.2, C7.2, C9.2, C10.2, C12.1, C13.1, C14.1, C15.1, C16.2, C17.1, C18.1, C19.1, C20.1, C21.1, C22.1, C30.2, C60.1, C61.2, D2.2 (VSS), D4.1 (K), D6.3 (GND), D7.3 (GND), D8.3 (GND), IC1.4 (GND), IC1.8 (DIR), IC2.6 (GND), IC2.15 (A0), IC2.16 (A1), J1.8 (BS1), J1.17 (VSS), J1.MP1, J1.MP2, J2.6 (VSS), J2.10 (GROUND_1), J2.11 (GROUND_2), J2.12 (GROUND_3), J2.13 (GROUND_4), J2.14 (GROUND_5), J2.15 (GROUND_6), JP1.1 (A), JP2.1 (A), JP3.1 (A), M1.SH1 (SHIELD), Q3.2 (E), R12.2, R13.2, SW1.1, SW2.1, SW3.1, SW4.1, SW5.1, SW6.1, SW7.1, U1.1 (GND), U1.2 (GND), U1.11 (GND), U1.14 (GND), U1.36 (GND), U1.37 (GND), U1.38 (GND), U1.39 (GND), U1.40 (GND), U1.41 (GND), U1.42 (GND), U1.43 (GND), U1.44 (GND), U1.45 (GND), U1.46 (GND), U1.47 (GND), U1.48 (GND), U1.49 (GND), U1.50 (GND), U1.51 (GND), U1.52 (GND), U1.53 (GND); also elsewhere on the board
unnamed: C8.2, D1.2 (A), M1.N, Q3.3 (C)
unnamed: C11.2, D3.1 (K), D4.2 (A)
unnamed: C11.1, D5.2 (A), L1.2, Q4.3 (D)
unnamed: IC1.5 (PGO), JP3.2 (B)
unnamed: C9.1, IC1.1 (VDD5V)
unnamed: C12.2, J1.5 (VSH2)
unnamed: Q1.1 (B), R7.2
unnamed: Q2.1 (B), R8.2
unnamed: Q3.1 (B), R9.2

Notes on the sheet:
this pull-up is larger, becouse i dont want to harm to fall times of the i2s clock
HOLES
addr(dec.):54
E-INK DISPLAY
addr(dec.):112
ESP32
I2C_1 PULL-UPs
MEMORY CARD SLOT
BUTONS
HAPTIC MOTOR
I/O EXPANDER
AUDIO
USB
LED
POWER
HAL EFFECT ENCODER
